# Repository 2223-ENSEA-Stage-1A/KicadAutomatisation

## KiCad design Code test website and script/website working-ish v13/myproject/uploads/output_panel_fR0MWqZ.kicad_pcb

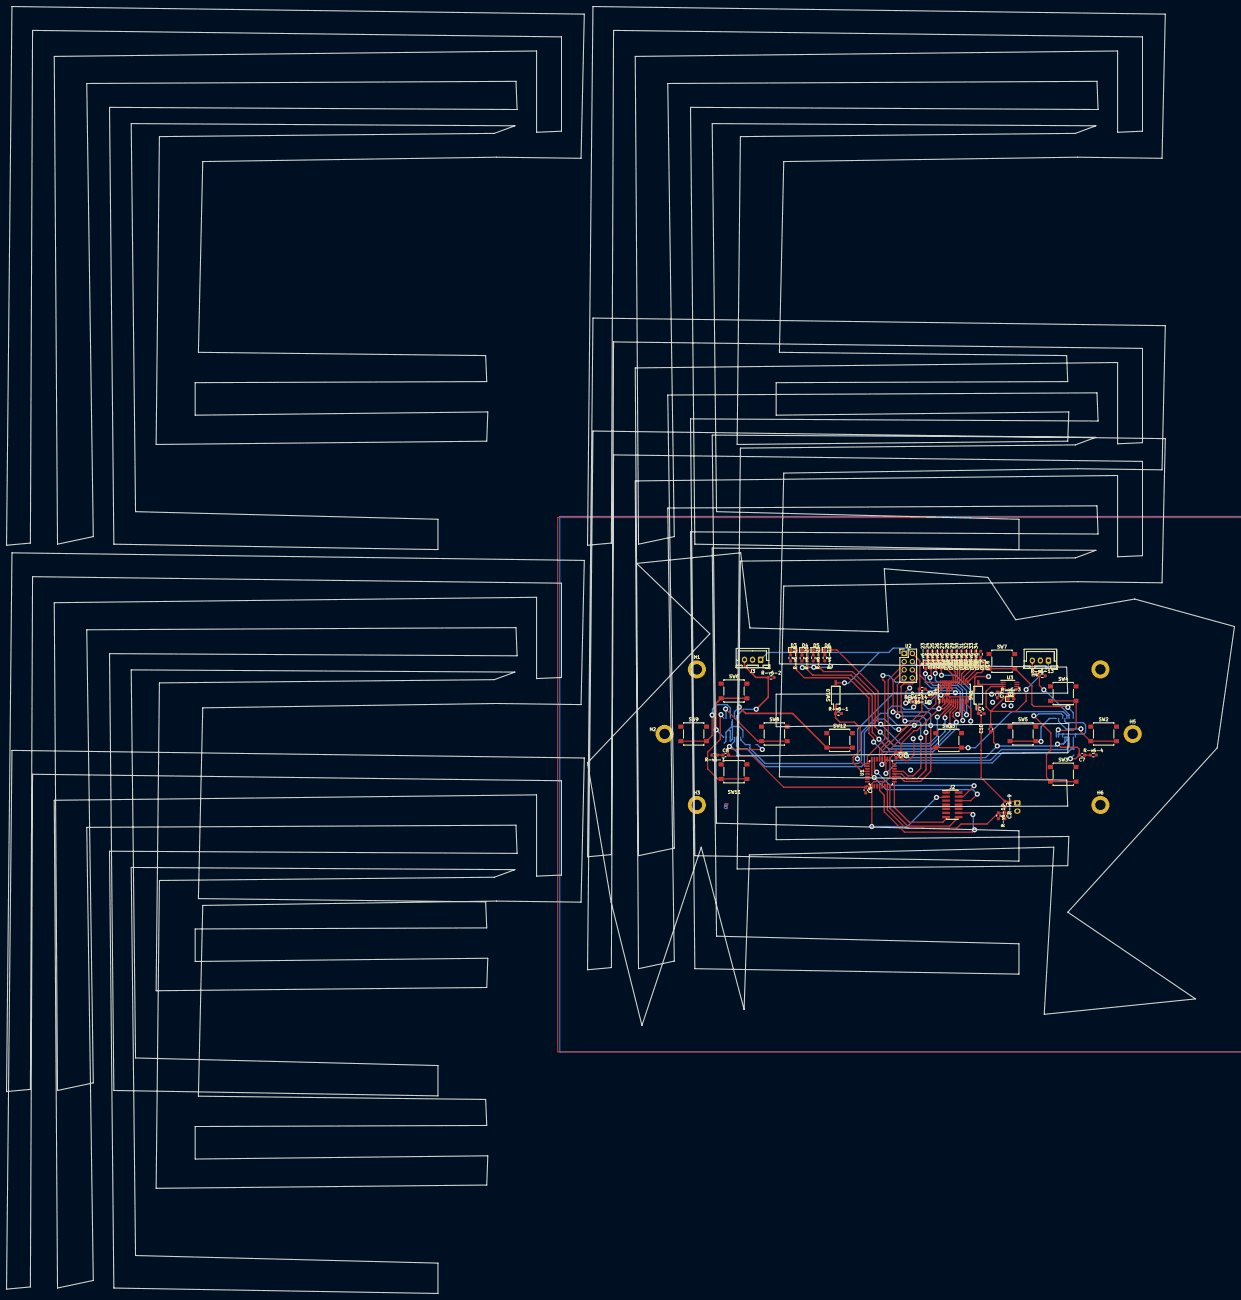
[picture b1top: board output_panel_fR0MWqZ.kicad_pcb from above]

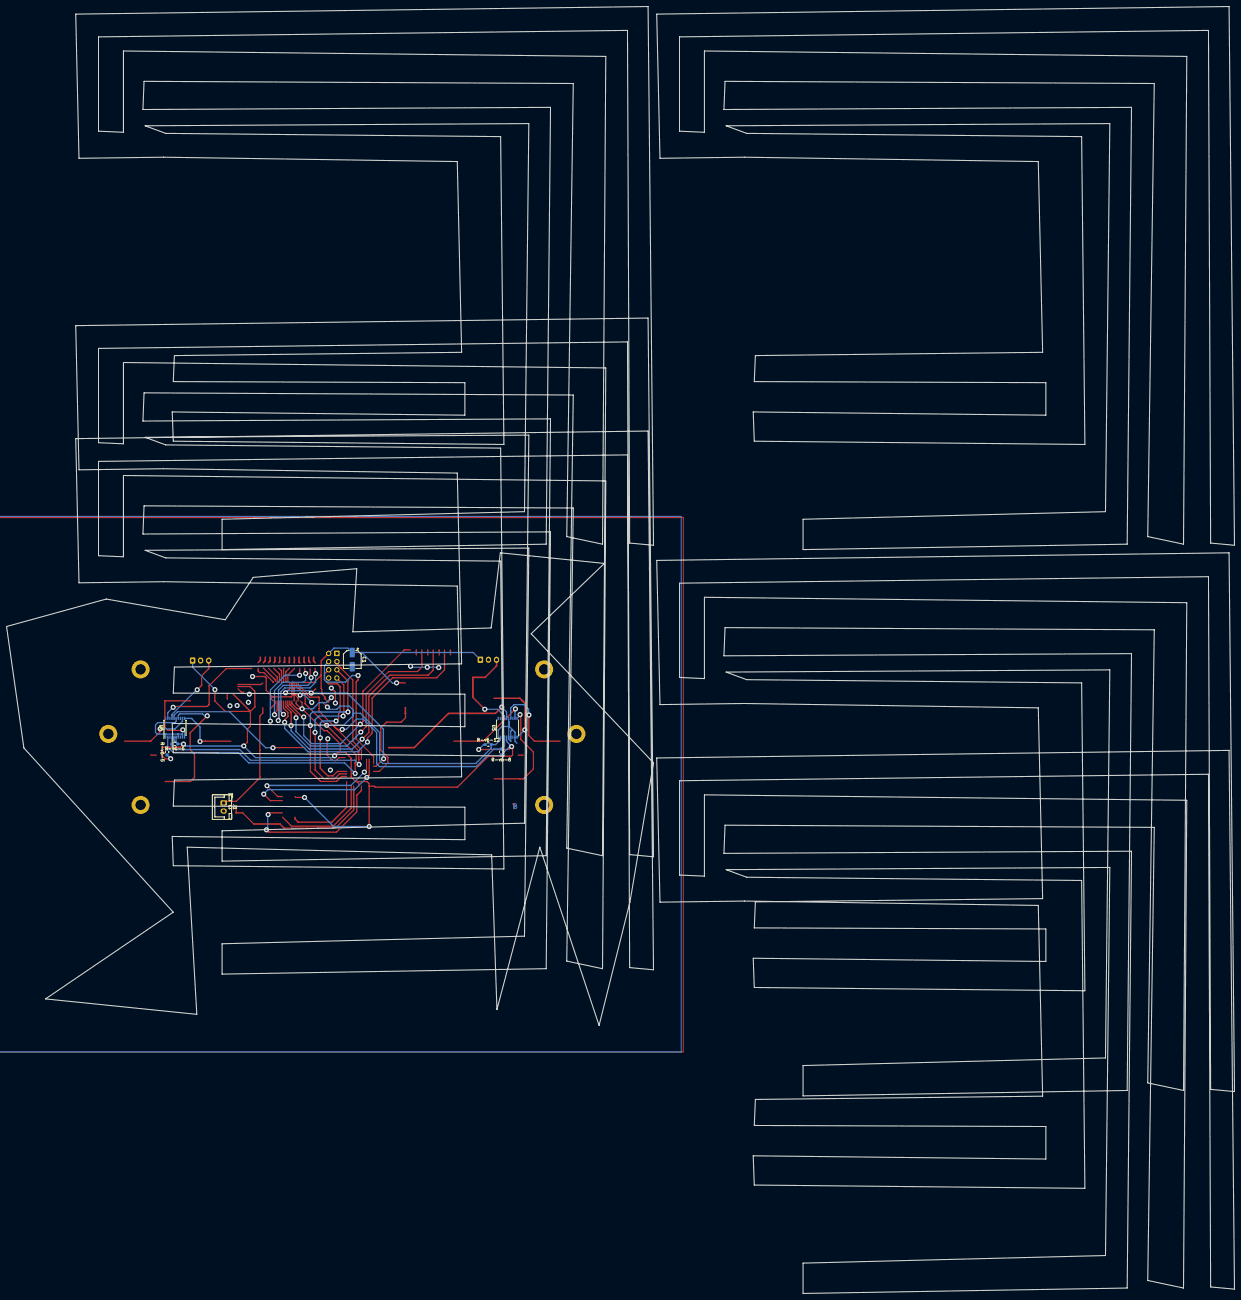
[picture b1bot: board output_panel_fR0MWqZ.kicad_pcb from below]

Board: 2 copper layers, 380.4 x 398.6 mm, 87 parts (8 on the bottom side), 68 nets.

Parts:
C1: 22uF; CP_Elec_5x5.4
C2: 1nF; C_0603_1608Metric_Pad1.08x0.95mm_HandSolder
C3, C5: 100n; C_0603_1608Metric_Pad1.08x0.95mm_HandSolder
C4: 1u; C_0603_1608Metric_Pad1.08x0.95mm_HandSolder
C6: 10u; C_0603_1608Metric_Pad1.08x0.95mm_HandSolder
C7, C8, C10: 100nF; C_0603_1608Metric_Pad1.08x0.95mm_HandSolder
C9: 470p; C_0603_1608Metric_Pad1.08x0.95mm_HandSolder
D2: L-v6-ED_Small; L-v6-ED_0603_1608Metric_Pad1.05x0.95mm_HandSolder
D3: G1; L-v6-ED_0603_1608Metric_Pad1.05x0.95mm_HandSolder
D4: G2; L-v6-ED_0603_1608Metric_Pad1.05x0.95mm_HandSolder
D5: G3; L-v6-ED_0603_1608Metric_Pad1.05x0.95mm_HandSolder
D6: G4; L-v6-ED_0603_1608Metric_Pad1.05x0.95mm_HandSolder
D7: G5; L-v6-ED_0603_1608Metric_Pad1.05x0.95mm_HandSolder
D8: G6; L-v6-ED_0603_1608Metric_Pad1.05x0.95mm_HandSolder
D9: G7; L-v6-ED_0603_1608Metric_Pad1.05x0.95mm_HandSolder
D10: G8; L-v6-ED_0603_1608Metric_Pad1.05x0.95mm_HandSolder
D11: O1; L-v6-ED_0603_1608Metric_Pad1.05x0.95mm_HandSolder
D12: O2; L-v6-ED_0603_1608Metric_Pad1.05x0.95mm_HandSolder
D13: O3; L-v6-ED_0603_1608Metric_Pad1.05x0.95mm_HandSolder
D14: O4; L-v6-ED_0603_1608Metric_Pad1.05x0.95mm_HandSolder
D15: R-v6-1; L-v6-ED_0603_1608Metric_Pad1.05x0.95mm_HandSolder
D16: R-v6-2; L-v6-ED_0603_1608Metric_Pad1.05x0.95mm_HandSolder
D17: R-v6-3; L-v6-ED_0603_1608Metric_Pad1.05x0.95mm_HandSolder
D18: R-v6-4; L-v6-ED_0603_1608Metric_Pad1.05x0.95mm_HandSolder
H1, H2, H3, H4, H5, H6: MountingHole_Pad; MountingHole_3.2mm_M3_DIN965_Pad
J1: Conn_01x02; JST_XH_B2B-XH-A_1x02_P2.50mm_Vertical
J2: Conn_02x07_Odd_Even; PinHeader_2x07_P1.27mm_Vertical_SMD
J3, J4: Conn_01x03; JST_XH_B3B-XH-A_1x03_P2.50mm_Vertical
R-v6-1, R-v6-2, R-v6-3, R-v6-13, R-v6-18, R-v6-20, R-v6-21, R-v6-22, R-v6-23, R-v6-24, R-v6-25, R-v6-26, R-v6-27, R-v6-28, R-v6-29, R-v6-30, R-v6-31, R-v6-32, R-v6-33, R-v6-34: 1K; R-v6-_0603_1608Metric_Pad0.98x0.95mm_HandSolder
R-v6-4, R-v6-7: 1k; R-v6-_0603_1608Metric_Pad0.98x0.95mm_HandSolder
R-v6-5, R-v6-6, R-v6-8, R-v6-11, R-v6-12, R-v6-14, R-v6-16: 10K; R-v6-_0603_1608Metric_Pad0.98x0.95mm_HandSolder
R-v6-9, R-v6-10: 1M; R-v6-_0603_1608Metric_Pad0.98x0.95mm_HandSolder
SW1, SW10: SW_DIP_x01; SW_DIP_SPSTx01_Slide_Copal_CHS-01B_W7.62mm_P1.27mm
SW2, SW3, SW4, SW5, SW6, SW8, SW9, SW11, SW12, SW13: SW_Push; SW_SPST_B3S-1000
SW7: SW_SPST; SW_SPST_B3S-1000
U1: STM32L-v6-412KBTx; L-v6-QFP-32_7x7mm_P0.8mm
U2: nR-v6-F24_Full; PinHeader_2x04_P2.54mm_Vertical
U3: MIC5219-3.3YMM; MSOP-8_3x3mm_P0.65mm
U4: PCA9685PW; TSSOP-28_4.4x9.7mm_P0.65mm
U5, U6: PCF8574TS; SSOP-20_4.4x6.5mm_P0.65mm

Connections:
A_Button-v6-: SW2.2, U6.12 (P2)
B_Button-v6-: SW3.2, U6.14 (P3)
CSN_nR-v6-F24: U1.25 (PA15), U2.4 (CSN)
DC_Button-v6-: SW11.2, U5.11 (P1)
DIODE_OE-v6-: R-v6-16.1, U1.26 (PB3), U4.23 (~OE)
DIO/EX_CL-v6-K: R-v6-5.2, R-v6-12.2, R-v6-14.2, U1.19 (PA9), U4.26 (SCL-v6-), U5.2 (SCL-v6-), U6.2 (SCL-v6-)
DIO/EX_SDA-v6-: R-v6-6.2, R-v6-8.2, R-v6-11.1, U1.20 (PA10), U4.27 (SDA), U5.4 (SDA), U6.4 (SDA)
Digital_Out_Put-v6-: U1.12 (PA6), U2.7 (MISO)
GND-v6-: C1.2, C2.2, C3.2, C4.2, C5.2, C6.2, C9.2, C10.2, D2.1 (K), H1.1, H2.1, H3.1, H4.1, H5.1, H6.1, J1.2, J2.5, J2.7, J2.11, J3.2, J4.2, R-v6-1.2, R-v6-2.2, R-v6-4.2, R-v6-7.2, R-v6-10.2, R-v6-13.2, R-v6-18.2, R-v6-20.2, R-v6-21.2, R-v6-22.2, R-v6-23.2, R-v6-24.2, R-v6-25.2, R-v6-26.2, R-v6-27.2, R-v6-28.2, R-v6-29.2, R-v6-30.2, R-v6-31.2, R-v6-32.2, R-v6-33.2, R-v6-34.2, SW2.1, SW3.1, SW4.1, SW5.1, SW6.1, SW7.1 (A), SW8.1, SW9.1, SW11.1, SW12.1, SW13.1, U1.16 (VSS), U1.32 (VSS), U2.1 (GND-v6-), U3.5 (GND-v6-), U3.6 (GND-v6-), U3.7 (GND-v6-), U3.8 (GND-v6-), U4.2 (A1), U4.4 (A3), U4.14 (VSS), U4.24 (A5), U4.25 (EXTCL-v6-K), U5.1 (~INT), U5.6 (A0), U5.7 (A1), U5.9 (A2), U5.15 (VSS), U6.1 (~INT), U6.7 (A1), U6.9 (A2), U6.15 (VSS)
Glob_Alim-v6-: C1.1, C3.1, C5.1, C6.1, C7.2, C8.2, C10.1, J2.3, J3.1, J4.1, R-v6-3.1, R-v6-5.1, R-v6-6.1, R-v6-8.1, R-v6-11.2, R-v6-12.1, R-v6-14.1, R-v6-16.2, SW10.2, U1.1 (VDD), U1.5 (VDDA), U1.17 (VDD), U2.2 (VCC), U3.3 (OUT), U4.1 (A0), U4.3 (A2), U4.5 (A4), U4.28 (VDD), U5.5 (VDD), U6.5 (VDD), U6.6 (A0)
L-v6-: J4.3, R-v6-13.1, U6.17 (P5)
L-v6-C_Button: SW8.2, U5.12 (P2)
L-v6-i-ion-v6-: C4.1, J1.1, R-v6-9.1, SW1.1
MOSI-v6-: U1.13 (PA7), U2.6 (MOSI-v6-)
NES/SNES_switcher-v6-: R-v6-1.1, SW10.1, U1.28 (PB5)
unnamed: SW1.2, U3.2 (IN)
unnamed: C7.1, R-v6-4.1
unnamed: C8.1, R-v6-7.1
unnamed: D2.2 (A), R-v6-3.2
unnamed: D3.2 (A), U4.9 (L-v6-ED3)
unnamed: D3.1 (K), R-v6-18.1
unnamed: D4.2 (A), U4.8 (L-v6-ED2)
unnamed: D4.1 (K), R-v6-20.1
unnamed: D5.2 (A), U4.7 (L-v6-ED1)
unnamed: D5.1 (K), R-v6-21.1
unnamed: D6.2 (A), U4.6 (L-v6-ED0)
unnamed: D6.1 (K), R-v6-22.1
unnamed: D7.2 (A), U4.10 (L-v6-ED4)
unnamed: D7.1 (K), R-v6-23.1
unnamed: D8.2 (A), U4.11 (L-v6-ED5)
unnamed: D8.1 (K), R-v6-24.1
unnamed: D9.2 (A), U4.12 (L-v6-ED6)
unnamed: D9.1 (K), R-v6-25.1
unnamed: D10.2 (A), U4.13 (L-v6-ED7)
unnamed: D10.1 (K), R-v6-26.1
unnamed: D11.2 (A), U4.22 (L-v6-ED15)
unnamed: D11.1 (K), R-v6-27.1
unnamed: D12.2 (A), U4.21 (L-v6-ED14)
unnamed: D12.1 (K), R-v6-28.1
unnamed: D13.2 (A), U4.20 (L-v6-ED13)
unnamed: D13.1 (K), R-v6-29.1
unnamed: D14.2 (A), U4.19 (L-v6-ED12)
unnamed: D14.1 (K), R-v6-30.1
unnamed: D15.2 (A), U4.18 (L-v6-ED11)
unnamed: D15.1 (K), R-v6-31.1
unnamed: D16.2 (A), U4.17 (L-v6-ED10)
unnamed: D16.1 (K), R-v6-32.1
unnamed: D17.2 (A), U4.16 (L-v6-ED9)
unnamed: D17.1 (K), R-v6-33.1
unnamed: D18.2 (A), U4.15 (L-v6-ED8)
unnamed: D18.1 (K), R-v6-34.1
unnamed: C9.1, U3.4 (BP)
Order_Search-v6-: SW7.2 (B), U6.19 (P6)
POWER-v6-_CHECK-v6-: C2.1, R-v6-9.2, R-v6-10.1, U1.7 (PA1)
Pin_Clock-v6-: U1.11 (PA5), U2.5 (SCK)
R-v6-: J3.3, R-v6-2.1, U5.17 (P5)
R-v6-C_Button: SW9.2, U5.14 (P3)
R-v6-X/TX: U1.21 (PA11), U2.3 (CE)
R-v6-eset_Buton -v6-: J2.12, U1.4 (NR-v6-ST)
SE_Button-v6-: SW13.2, U6.16 (P4)
ST_Button-v6-: SW12.2, U5.16 (P4)
SWDCK-v6-: J2.6, U1.24 (PA14)
SWDIO-v6-: J2.4, U1.23 (PA13)
UC_Button-v6-: SW6.2, U5.10 (P0)
USAR-v6-T2_R-v6-X-v6-: J2.13, U1.9 (PA3)
USAR-v6-T2_TX-v6-: J2.14, U1.8 (PA2)
X_Button-v6-: SW4.2, U6.10 (P0)
Y_Button-v6-: SW5.2, U6.11 (P1)

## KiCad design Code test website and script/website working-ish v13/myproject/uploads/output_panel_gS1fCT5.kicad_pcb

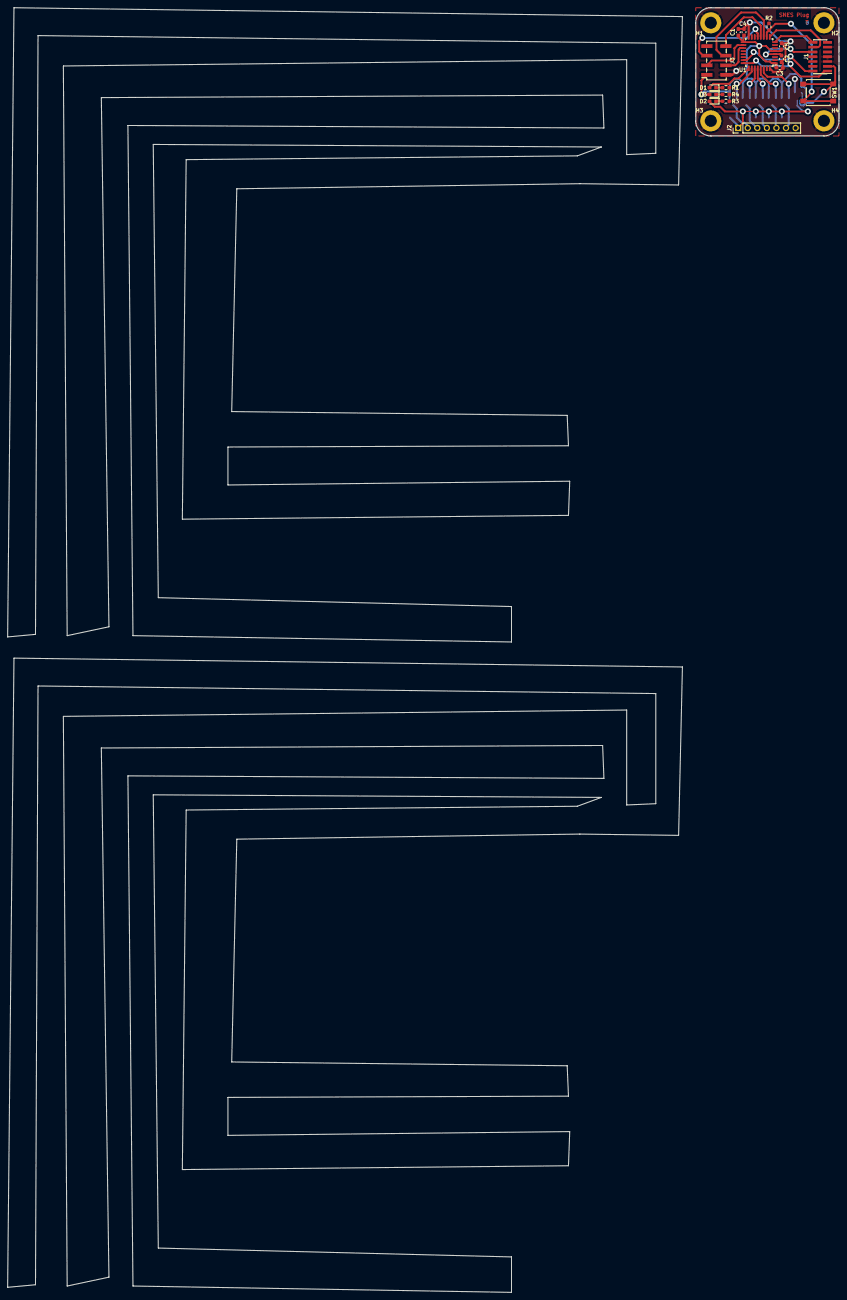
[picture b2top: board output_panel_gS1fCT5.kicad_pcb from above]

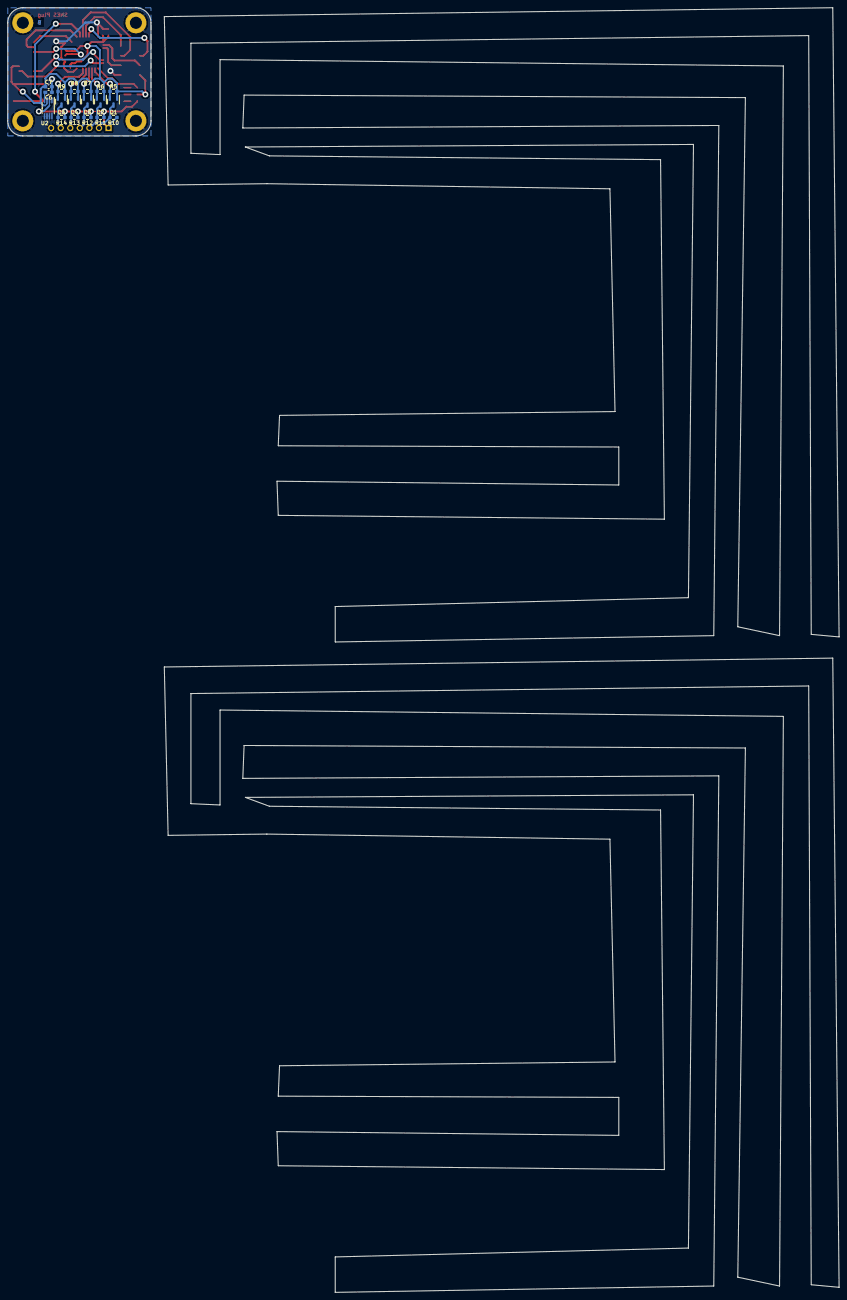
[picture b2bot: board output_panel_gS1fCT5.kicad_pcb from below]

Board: 2 copper layers, 220.5 x 340.7 mm, 39 parts (18 on the bottom side), 29 nets.

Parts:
C1: 10u; C_0603_1608Metric_Pad1.08x0.95mm_HandSolder
C2, C3, C4, C5: 100n; C_0603_1608Metric_Pad1.08x0.95mm_HandSolder
C6: 470p; C_0603_1608Metric_Pad1.08x0.95mm_HandSolder
C7: 2.2u; C_0603_1608Metric_Pad1.08x0.95mm_HandSolder
D1, D2: LED_Small; D_0603_1608Metric_Pad1.05x0.95mm_HandSolder
D3: LED; D_0603_1608Metric_Pad1.05x0.95mm_HandSolder
H1, H2, H3, H4: MountingHole_Pad; MountingHole_3.2mm_M3_DIN965_Pad
J1: Conn_02x07_Odd_Even; PinHeader_2x07_P1.27mm_Vertical_SMD
J2: Conn_01x07_Socket; PinHeader_1x07_P2.54mm_Vertical
J3: Conn_01x08_Socket; PinSocket_2x04_P2.54mm_Vertical_SMD
Q1, Q2, Q3, Q4, Q5: 2N7002; SOT-23
R1, R3, R4: 1k; R_0603_1608Metric_Pad0.98x0.95mm_HandSolder
R2, R5, R6, R7, R8, R9, R10, R11, R12, R13, R14: 10k; R_0603_1608Metric_Pad0.98x0.95mm_HandSolder
SW1: SW_SPST; SW_SPST_B3S-1000
U1: STM32L412KBTx; LQFP-32_7x7mm_P0.8mm
U2: MIC5219-3.3YMM; MSOP-8_3x3mm_P0.65mm

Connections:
+3.3V-v2-: C1.1, C3.1, C4.1, C5.1, C7.1, D3.2 (A), J1.3, J3.1, Q1.1 (G), Q2.1 (G), Q3.1 (G), Q4.1 (G), Q5.1 (G), R5.1, R6.1, R7.1, R8.1, R9.1, SW1.2 (B), U1.1 (VDD), U1.5 (VDDA), U1.17 (VDD), U2.3 (OUT)
+5V-v2-: D2.2 (A), J2.1, R10.1, R11.1, R12.1, R13.1, R14.1, U2.2 (IN)
Appairing_Btn-v2-: R2.1, SW1.1 (A), U1.10 (PA4)
Chip_Enable-v2-: J3.4, U1.19 (PA9)
Data_Clock_SNES-v2-: J2.2, Q1.3 (D), R10.2
Data_Clock_STM32-v2-: Q1.2 (S), R5.2, U1.26 (PB3)
Data_Latch_SNES-v2-: J2.3, Q2.3 (D), R11.2
Data_Latch_STM32-v2-: Q2.2 (S), R6.2, U1.27 (PB4)
GND-v2-: C1.2, C2.1, C3.2, C4.2, C5.2, C6.2, C7.2, H1.1, H2.1, H3.1, H4.1, J1.5, J1.7, J1.11, J2.7, J3.2, R1.2, R2.2, R3.2, R4.2, U1.16 (VSS), U1.32 (VSS), U2.5 (GND-v2-), U2.6 (GND-v2-), U2.7 (GND-v2-), U2.8 (GND-v2-)
IOBit_SNES-v2-: J2.6, Q5.3 (D), R14.2
IOBit_STM32-v2-: Q5.2 (S), R9.2, U1.30 (PB7)
NRST-v2-: C2.2, J1.10, U1.4 (NRST-v2-)
unnamed: D1.1 (K), R1.1
unnamed: D2.1 (K), R3.1
unnamed: D3.1 (K), R4.1
unnamed: C6.1, U2.4 (BP)
SPI_Chip_Select-v2-: J3.3, U1.18 (PA8)
SPI_Clock-v2-: J3.6, U1.11 (PA5)
SPI_Digital_Input-v2-: J3.8, U1.12 (PA6)
SPI_Digital_Output-v2-: J3.5, U1.13 (PA7)
SWDCK-v2-: J1.1, U1.24 (PA14)
SWDIO-v2-: J1.2, U1.23 (PA13)
Serial_Data1_SNES-v2-: J2.4, Q3.3 (D), R12.2
Serial_Data1_STM32-v2-: Q3.2 (S), R7.2, U1.28 (PB5)
Serial_Data2_SNES-v2-: J2.5, Q4.3 (D), R13.2
Serial_Data2_STM32-v2-: Q4.2 (S), R8.2, U1.29 (PB6)
Status_LED-v2-: D1.2 (A), U1.25 (PA15)
USART2_RX-v2-: J1.12, U1.9 (PA3)
USART2_TX-v2-: J1.14, U1.8 (PA2)
